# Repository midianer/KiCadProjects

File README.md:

# KiCadProjects
Kicad project eload

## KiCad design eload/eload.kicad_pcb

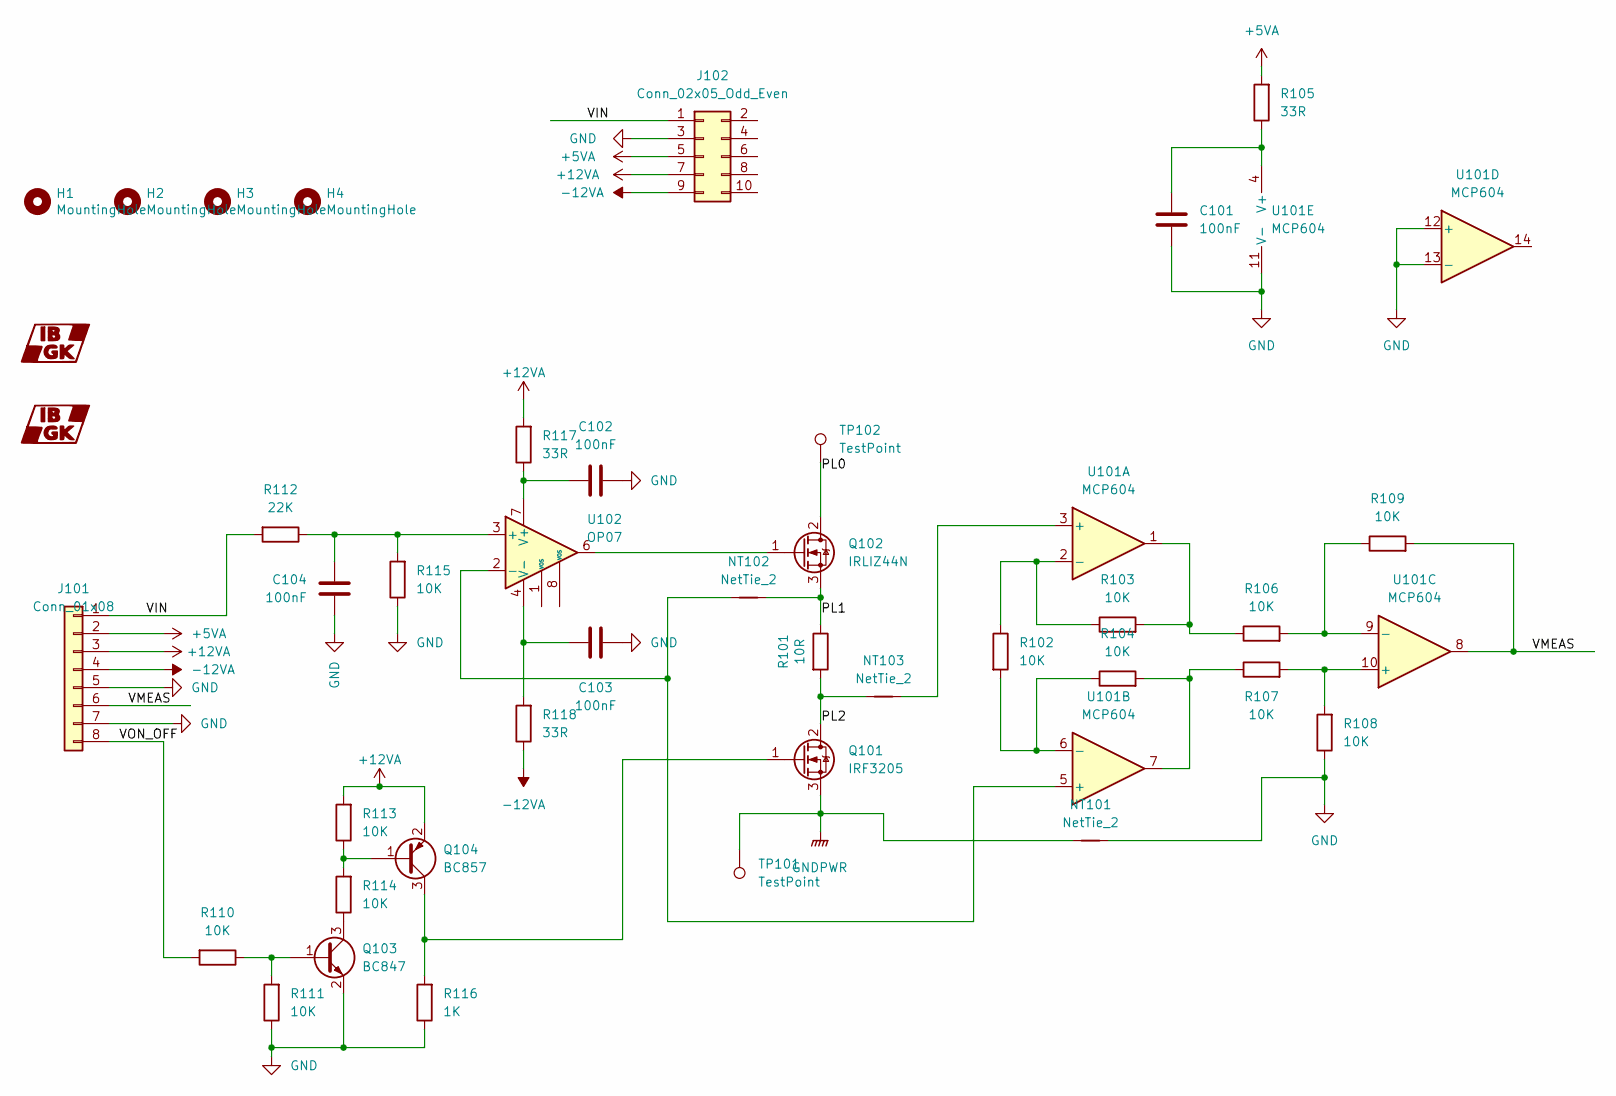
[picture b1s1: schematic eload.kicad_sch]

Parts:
C101, C102, C103, C104: C; C_1206_3216Metric_Pad1.33x1.80mm_HandSolder
G1: LOGO; iblogo
G2: LOGO; iblogo_Cu
H1, H2, H3, H4: MountingHole; MountingHole_3.2mm_M3_Pad_TopBottom
J101: Conn_01x08; PinHeader_1x08_P2.54mm_Vertical
J102: Conn_02x05_Odd_Even; IDC-Header_2x05_P2.54mm_Vertical
NT101, NT102, NT103: NetTie_2; NetTie-2_SMD_Pad0.5mm
Q101: IRF3205; TO-220F-3_Vertical
Q102: IRLIZ44N; TO-220F-3_Vertical
Q103: BC847; SOT-23
Q104: BC857; SOT-23
R101: 10R; R_Axial_Power_L25.0mm_W6.4mm_P27.94mm
R102, R103, R104, R106, R107, R108, R109, R110, R111, R113, R114, R115: 10K; R_0805_2012Metric_Pad1.20x1.40mm_HandSolder
R105, R117, R118: 33R; R_0805_2012Metric_Pad1.20x1.40mm_HandSolder
R112: 22K; R_0805_2012Metric_Pad1.20x1.40mm_HandSolder
R116: 1K; R_0805_2012Metric_Pad1.20x1.40mm_HandSolder
TP101, TP102: TestPoint; TestPoint_THTPad_3.0x3.0mm_Drill1.5mm
U101: MCP604; SO-14_3.9x8.65mm_P1.27mm
U102: OP07; SO-8_3.9x4.9mm_P1.27mm

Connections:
+5VA: J101.2, J102.5, R105.2
+12VA: J101.3, J102.7, Q104.2 (E), R113.2, R117.2
-12VA: J101.4, J102.9, R118.1
/PL0: Q102.2 (D), TP102.1
/PL1: NT102.2, Q102.3 (S), R101.1
/PL2: NT103.1, Q101.2 (D), R101.2
/VIN: J101.1, J102.1, R112.2
/VMEAS: J101.6, R109.2, U101.8
/VON_OFF: J101.8, R110.2
GND: C101.2, C102.2, C103.2, C104.2, J101.5, J101.7, J102.3, NT101.2, Q103.2 (E), R108.1, R111.1, R115.1, R116.1, U101.11 (V-), U101.12 (+), U101.13 (-); also elsewhere on the board
GNDPWR: NT101.1, Q101.3 (S), TP101.1
unnamed 11: C101.1, R105.1, U101.4 (V+); also elsewhere on the board
unnamed 12: C102.1, R117.1, U102.7 (V+); also elsewhere on the board
unnamed 13: C103.1, R118.2, U102.4 (V-); also elsewhere on the board
unnamed 14: C104.1, R112.1, R115.2, U102.3 (+); also elsewhere on the board
unnamed: NT102.1, U101.5 (+), U102.2 (-)
unnamed: Q101.1 (G), Q104.3 (C), R116.2
unnamed: Q102.1 (G), U102.6
unnamed: Q103.1 (B), R110.1, R111.2
unnamed: Q103.3 (C), R114.1
unnamed: Q104.1 (B), R113.1, R114.2
unnamed: R102.1, R103.1, U101.2 (-)
unnamed: R102.2, R104.1, U101.6 (-)
unnamed: R103.2, R106.1, U101.1
unnamed: R104.2, R107.1, U101.7
unnamed: R106.2, R109.1, U101.9 (-)
unnamed: R107.2, R108.2, U101.10 (+)
unnamed: NT103.2, U101.3 (+)

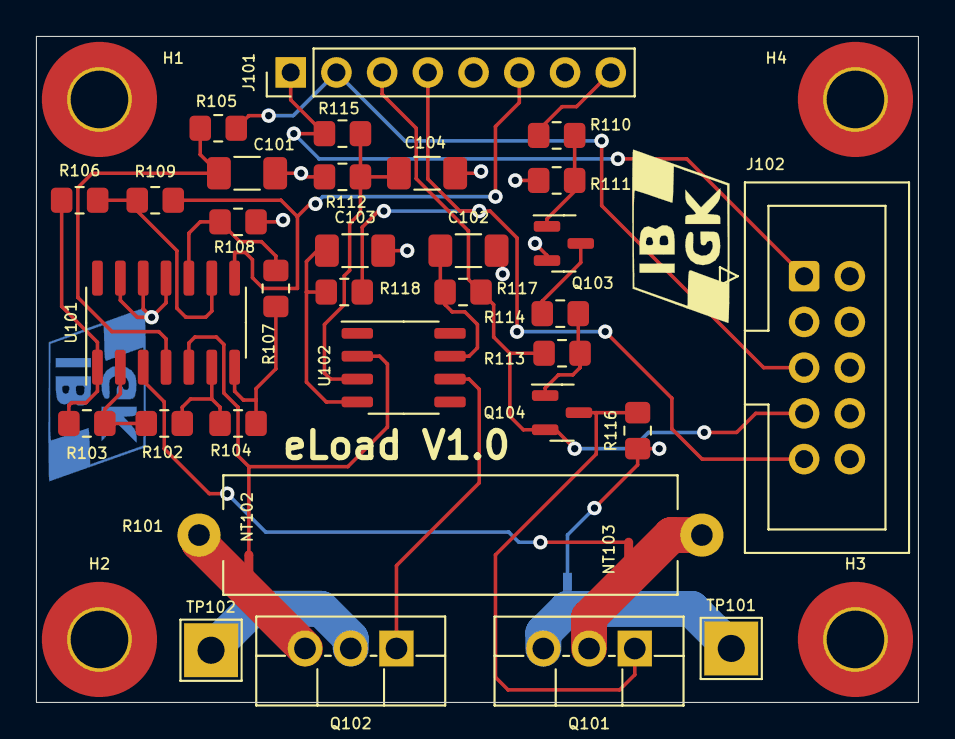
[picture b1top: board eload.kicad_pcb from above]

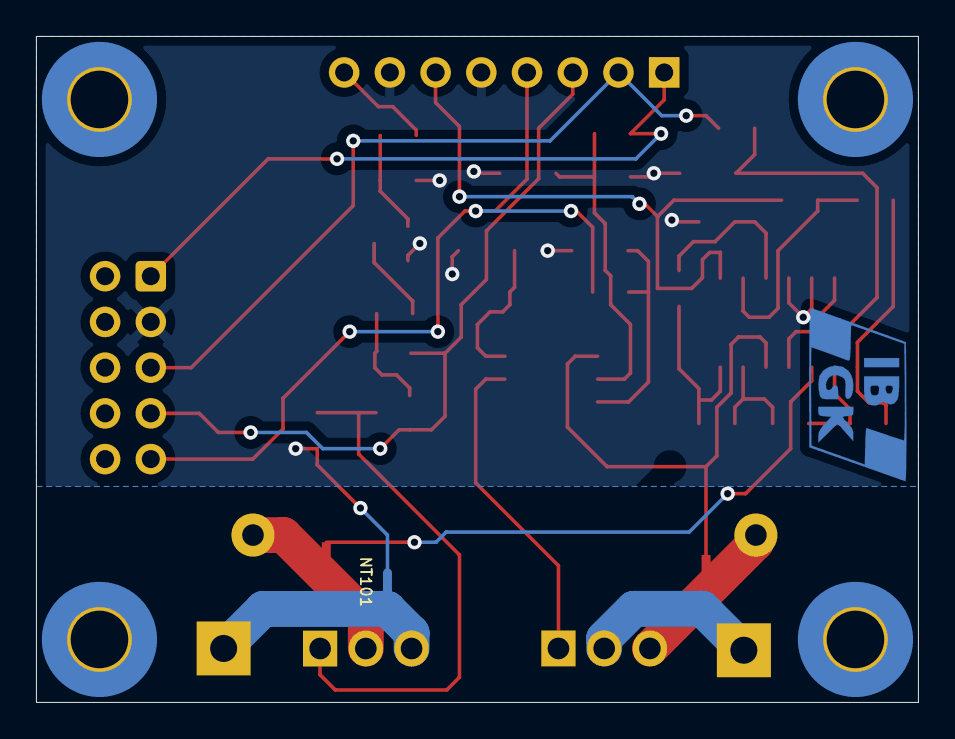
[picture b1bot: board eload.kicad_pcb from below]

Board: 2 copper layers, 49.0 x 37.0 mm, 41 parts (2 on the bottom side), 28 nets.

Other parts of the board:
C?: C; C_1206_3216Metric_Pad1.33x1.80mm_HandSolder
C?#2, C?#3, C?#4: C; C_1206_3216Metric_Pad1.33x1.80mm_HandSolder

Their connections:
GND: C?.2, C?#2.2, C?#3.2, C?#4.2; also elsewhere on the board
unnamed 11: C?#3.1; also elsewhere on the board
unnamed 12: C?#4.1; also elsewhere on the board
unnamed 13: C?.1; also elsewhere on the board
unnamed 14: C?#2.1; also elsewhere on the board

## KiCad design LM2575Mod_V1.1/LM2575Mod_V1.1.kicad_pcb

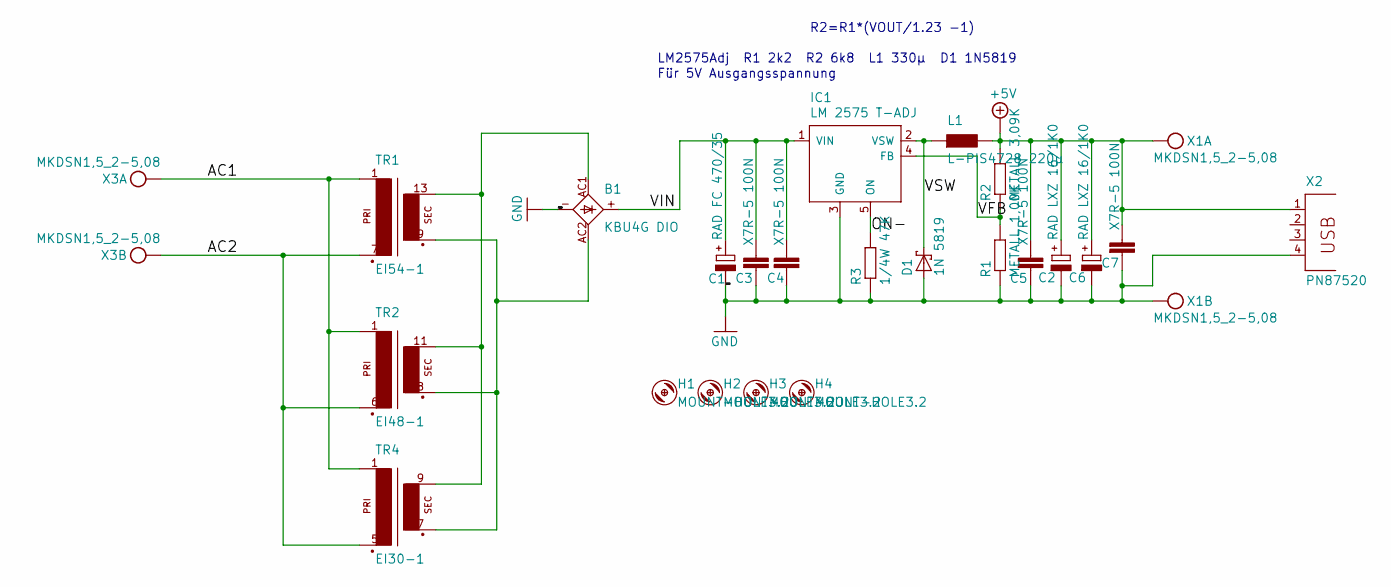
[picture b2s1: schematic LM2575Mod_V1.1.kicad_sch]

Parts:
B1: KBU4G DIO; KBU
C1: RAD FC 470/35; E5-8,5
C2, C6: RAD LXZ 16/1K0; E5-8,5
C3, C4, C5, C7: X7R-5 100N; C050-025X075
D1: 1N 5819; DO35-10-1
H1, H2, H3, H4: MOUNT-HOLE3.2; 3,2
IC1: LM 2575 T-ADJ; TO220-5
L1: L-PIS4728 220µ; PIS4728
R1: METALL 1,00K; 0207_10
R2: METALL 3,09K; 0207_10
R3: 1/4W 47K; 0207_10
TR1: EI54-1
TR2: EI48-1
TR4: EI30-1
X1, X3: MKDSN1,5_2-5,08
X2: PN87520

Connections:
+5V: C2.+, C5.1, C6.+, C7.1, L1.P$2, R2.2, X1.1 (KL), X2.1
/AC1: TR1.1, TR2.1, TR4.1, X3.1 (KL)
/AC2: TR1.7 (P2), TR2.6 (P2), TR4.5 (P2), X3.2 (KL)
/ON-: IC1.5 (ON), R3.2
/VFB: IC1.4 (FB), R1.2, R2.1
/VIN: B1.+, C1.+, C3.1, C4.1, IC1.1 (VIN)
/VSW: D1.C, IC1.2 (VSW), L1.P$1
GND: B1.-, C1.-, C2.-, C3.2, C4.2, C5.2, C6.-, C7.2, D1.A, IC1.3 (GND), R1.1, R3.1, X1.2 (KL), X2.4
unnamed: B1.AC1, TR1.13 (S4), TR2.11 (S4), TR4.9 (S4)
unnamed: B1.AC2, TR1.9 (S3), TR2.8 (S3), TR4.7 (S3)

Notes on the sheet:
Für 5V Ausgangsspannung
LM2575Adj R1 2k2 R2 6k8 L1 330µ D1 1N5819
R2=R1*(VOUT/1.23 -1)

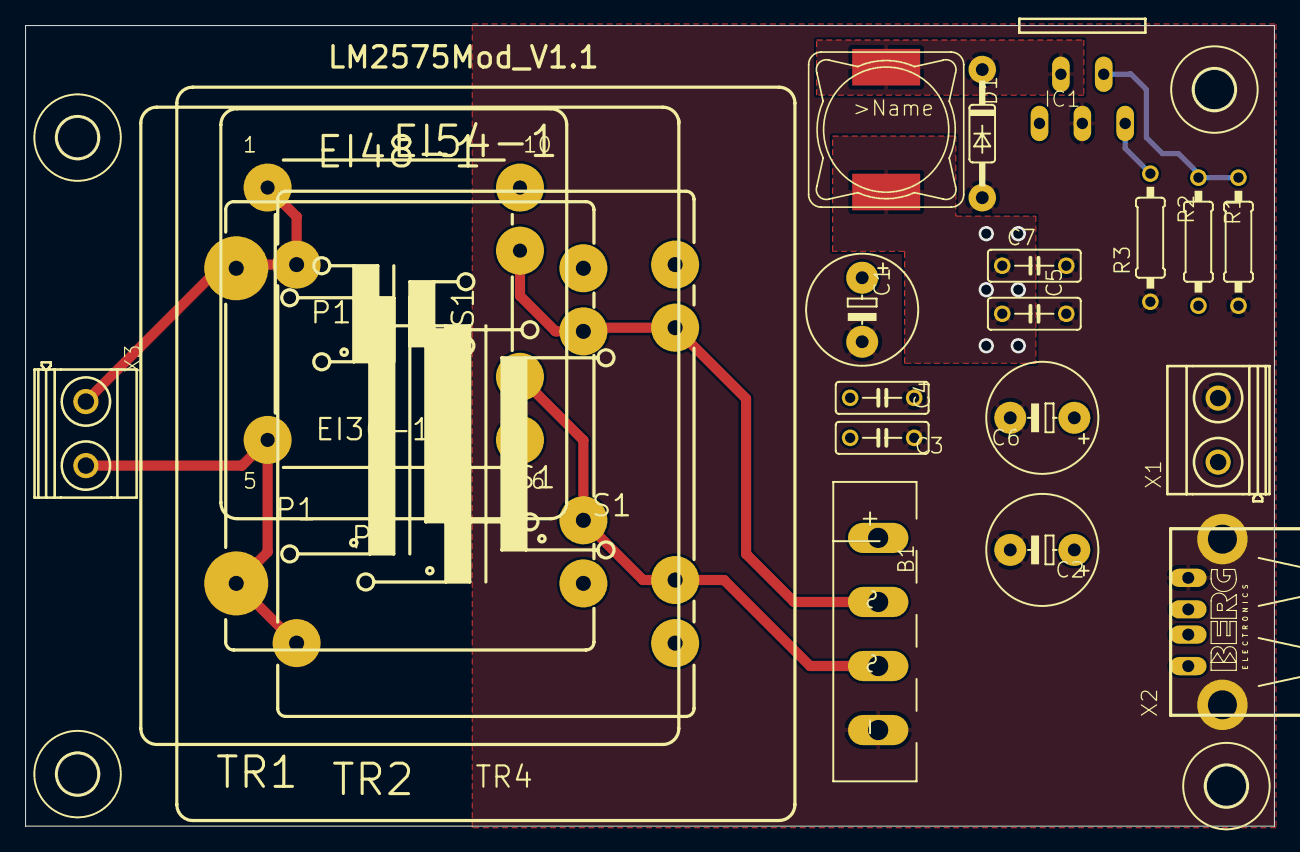
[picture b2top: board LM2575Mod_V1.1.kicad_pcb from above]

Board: 2 copper layers, 99.1 x 63.5 mm, 24 parts (0 on the bottom side), 10 nets.

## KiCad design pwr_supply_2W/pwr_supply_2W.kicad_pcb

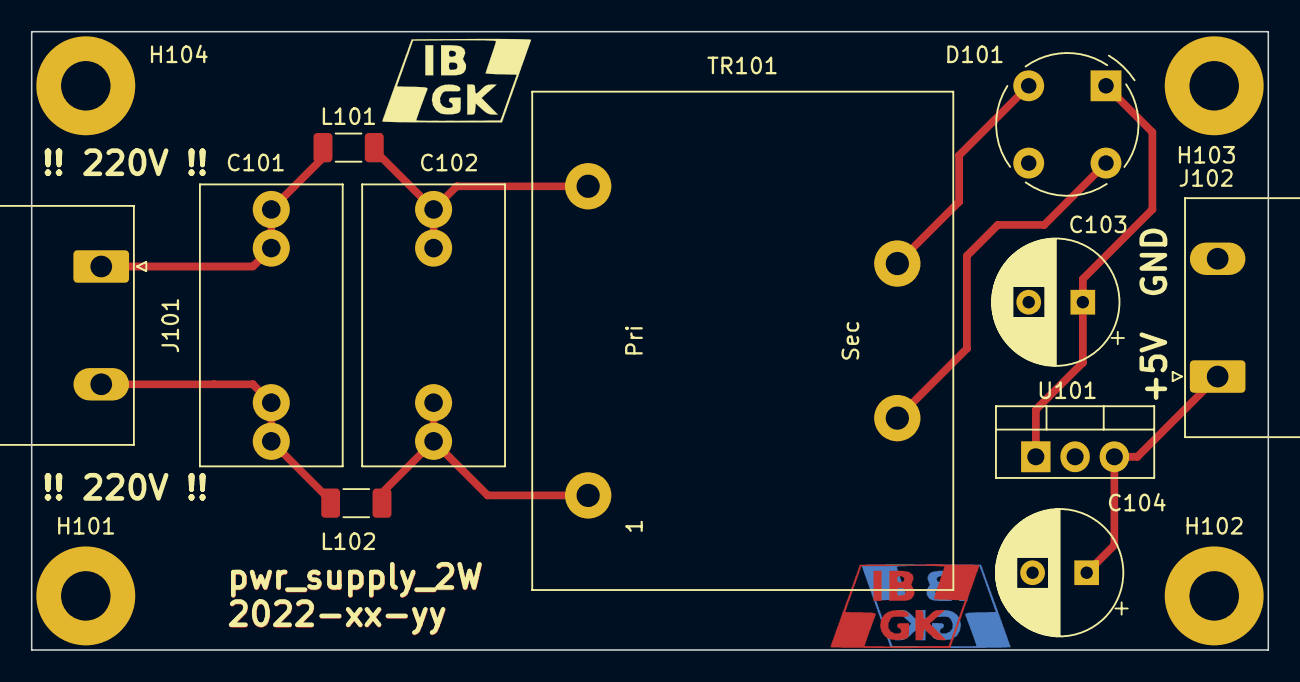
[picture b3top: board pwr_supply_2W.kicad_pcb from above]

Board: 2 copper layers, 80.0 x 40.0 mm, 18 parts (1 on the bottom side), 9 nets.

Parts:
C101: 100nF; C_Rect_L18.0mm_W9.0mm_P15.00mm_FKS3_FKP3
C104: 470uF/25V; CP_Radial_D8.0mm_P3.50mm
C?: C; C_Rect_L18.0mm_W9.0mm_P15.00mm_FKS3_FKP3
C?#2: 470uF/25V; CP_Radial_D8.0mm_P3.50mm
D?: D_Bridge_+A-A; Diode_Bridge_Round_D9.0mm
G101: LOGO; iblogo
G102, G103: LOGO; iblogo_Cu
H101, H102, H103, H104: MountingHole; MountingHole_3.2mm_M3_Pad
J?: Conn_01x02; PhoenixContact_GMSTBA_2,5_2-G-7,62_1x02_P7.62mm_Horizontal
J?#2: Conn_01x02; PhoenixContact_GMSTBA_2,5_2-G-7,62_1x02_P7.62mm_Horizontal
L102: BLM31 100u; L_1206_3216Metric_Pad1.22x1.90mm_HandSolder
L?: L; L_1206_3216Metric_Pad1.22x1.90mm_HandSolder
TR101: EI30/18 9V; Transformer_CHK_EI30-2VA_1xSec
U?: LM7805_TO220; TO-220-3_Vertical

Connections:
/220V_AC1: C101.1, J?#2.1, L?.1
/220V_AC1_F: C?.1, L?.2, TR101.1
/220V_AC2: C101.2, J?#2.2, L102.1
/220V_AC2_F: C?.2, L102.2, TR101.5
/+5V: C104.1, J?.1, U?.3 (VO)
/AC1: D?.4, TR101.7
/AC2: D?.2, TR101.9
/GND: C104.2, C?#2.2, D?.3 (-), J?.2, U?.2 (GND)
/VP: C?#2.1, D?.1 (+), U?.1 (VI)

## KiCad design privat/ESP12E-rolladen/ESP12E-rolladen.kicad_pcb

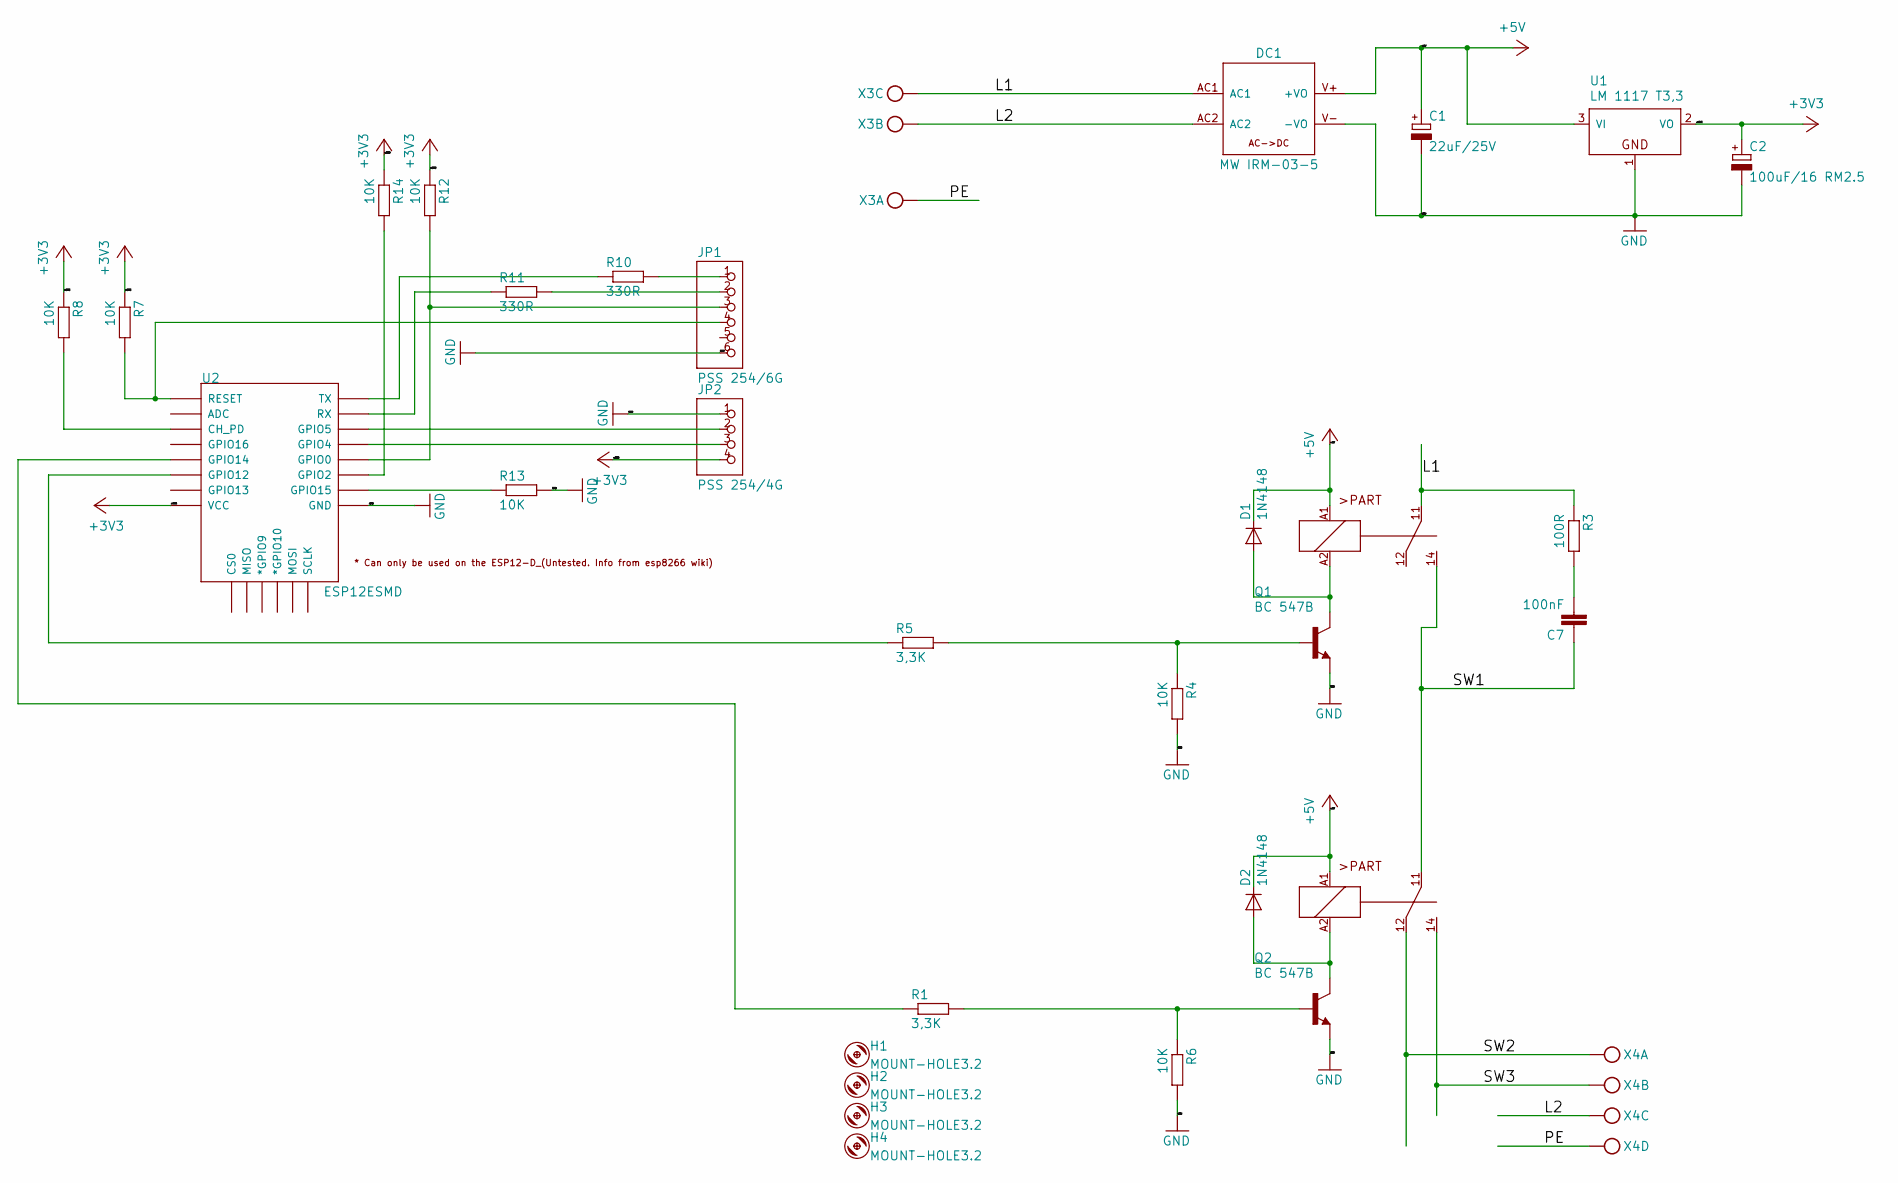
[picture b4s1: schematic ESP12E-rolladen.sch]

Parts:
C1: 22uF/25V; CRAD_E2,5-6
C2: 100uF/16 RM2.5; CRAD_E2,5-6
C7: 100nF; C150-054X183
D1, D2: 1N4148; 1N4148-DO35_4
DC1: MW IRM-03-5; MW_IRM03
H1, H2, H3, H4: MOUNT-HOLE3.2; 3,2
JP1: PSS 254/6G; 1X06
JP2: PSS 254/4G; 1X04
K2, K3: FTR LYCA 005V; FTR_LY
Q1, Q2: BC 547B; TO92
R1, R5: 3,3K; R1206
R3: 100R; 0411_15
R4, R6, R7, R8, R12, R13, R14: 10K; R1206
R10, R11: 330R; R1206
U1: LM 1117 T3,3; TO220S
U2: ESP12ESMD; ESP12E-SMD
X3: MKDSN1,5_3-5,08
X4: MKDSN1,5_4-5,08

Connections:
+3V3: C2.+, JP2.4, R7.1, R8.1, R12.1, R14.1, U1.2 (VO), U2.VCC
+5V: C1.+, D1.K, D2.K, DC1.V+ (+VO), K2.A1 (1), K3.A1 (1), U1.3 (VI)
/L1: DC1.AC1, K3.11 (S1), R3.1, X3.3
/L2: DC1.AC2, X3.2, X4.3
/PE: X3.1, X4.4
/SW1: C7.1, K2.11 (S1), K3.14 (A1)
/SW2: K2.12 (R1), X4.1
/SW3: K2.14 (A1), X4.2
GND: C1.-, C2.-, DC1.V- (-VO), JP1.6, JP2.1, Q1.1 (E), Q2.1 (E), R4.2, R6.2, R13.2, U1.1 (GND), U2.GND
unnamed: C7.2, R3.2
unnamed: D1.A, K3.A2 (2), Q1.3 (C)
unnamed: D2.A, K2.A2 (2), Q2.3 (C)
unnamed: JP1.1, R10.2
unnamed: JP1.2, R11.2
unnamed: JP1.3, R12.2, U2.GPIO0
unnamed: JP1.4, R7.2, U2.RESET
unnamed: JP2.2, U2.GPIO5
unnamed: JP2.3, U2.GPIO4
unnamed: Q1.2 (B), R4.1, R5.2
unnamed: Q2.2 (B), R1.2, R6.1
unnamed: R1.1, U2.GPIO14
unnamed: R5.1, U2.GPIO12
unnamed: R8.2, U2.CH_PD
unnamed: R10.1, U2.TXD0 (TX)
unnamed: R11.1, U2.RXD0 (RX)
unnamed: R13.1, U2.GPIO15
unnamed: R14.2, U2.GPIO2

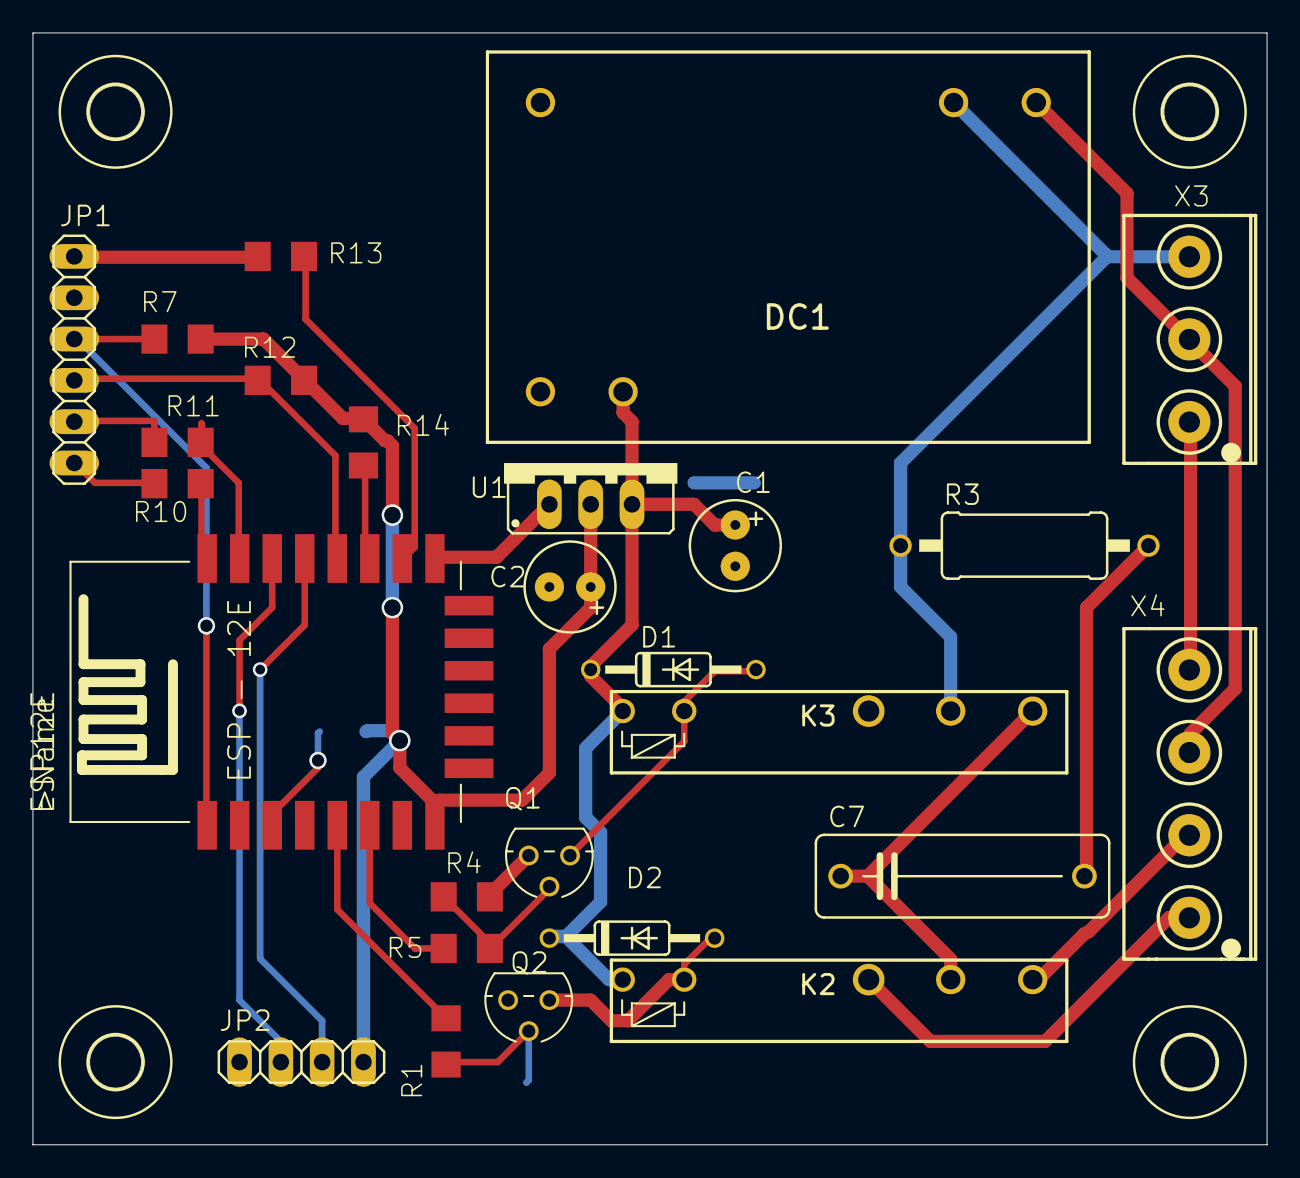
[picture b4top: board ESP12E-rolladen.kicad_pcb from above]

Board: 2 copper layers, 75.9 x 68.3 mm, 32 parts (0 on the bottom side), 27 nets.

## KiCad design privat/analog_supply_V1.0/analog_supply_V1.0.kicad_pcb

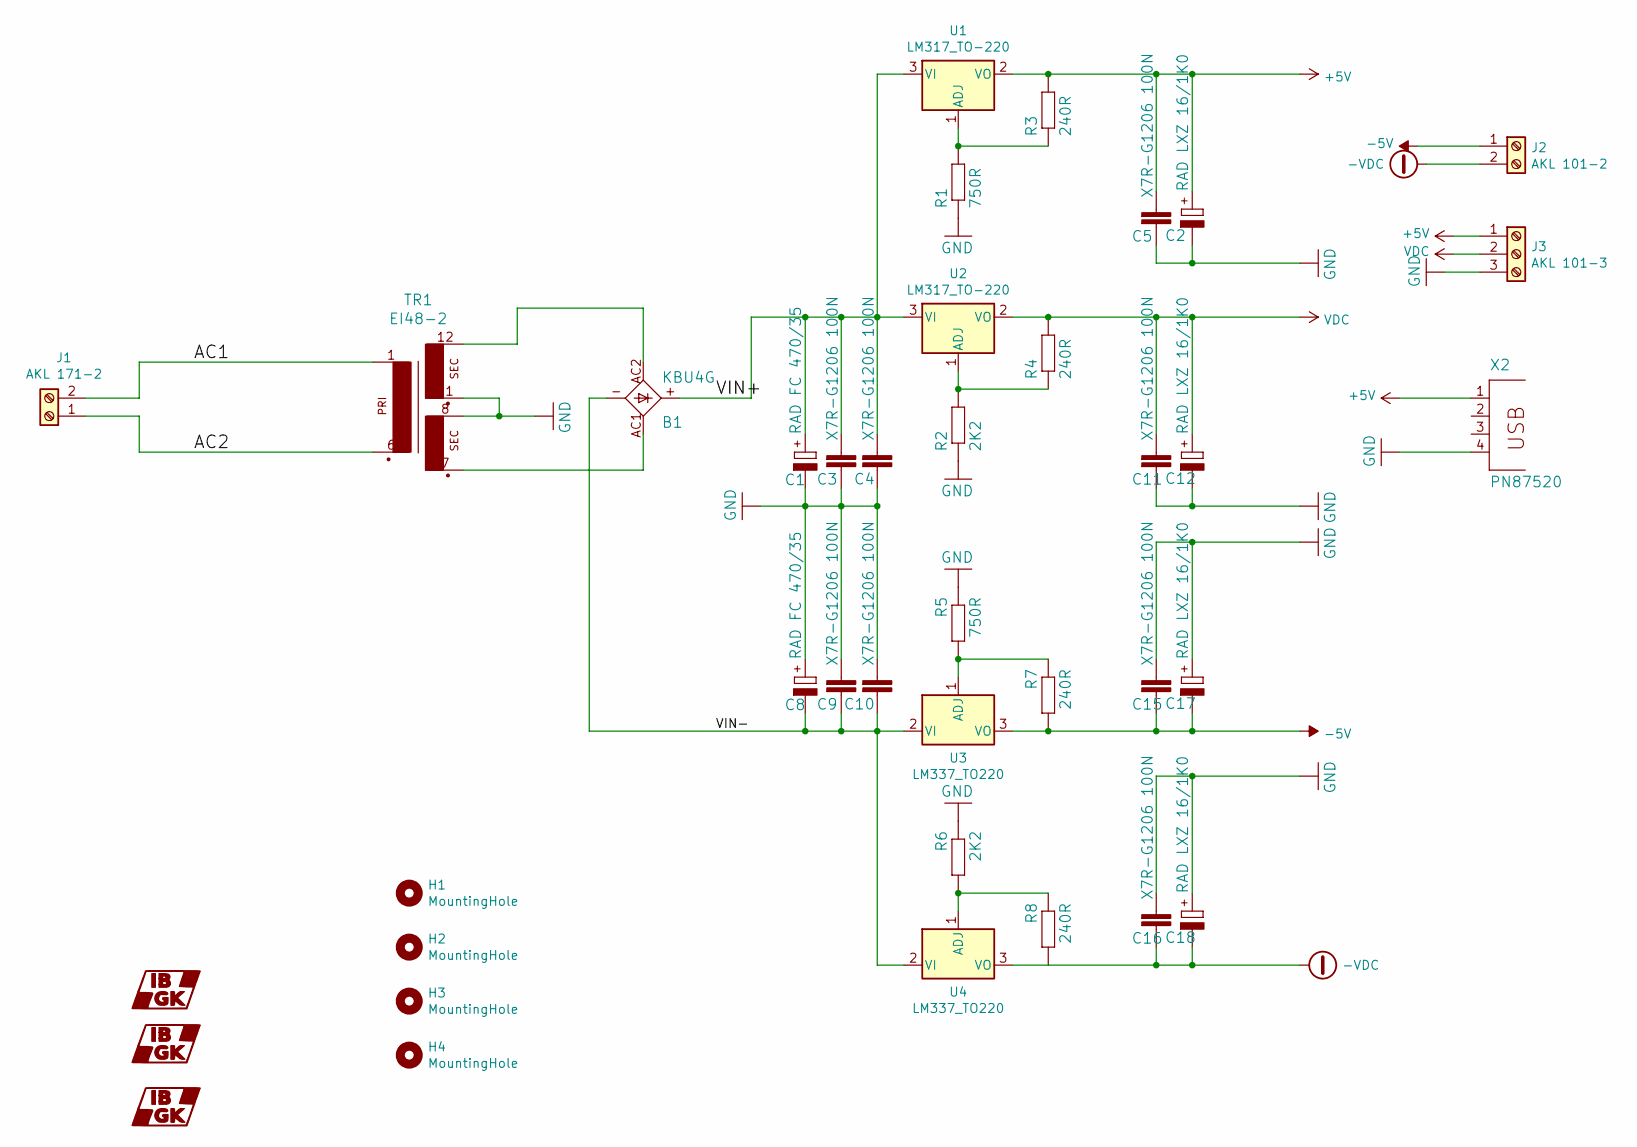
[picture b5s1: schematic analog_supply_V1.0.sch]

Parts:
B1: KBU4G; KBU
C1, C8: RAD FC 470/35; E5-8,5
C2, C12, C17, C18: RAD LXZ 16/1K0; E5-8,5
C3, C4, C5, C9, C10, C11, C15, C16: X7R-G1206 100N; C_1206_3216Metric_Pad1.33x1.80mm_HandSolder
G1: LOGO; iblogo
G2, G3: LOGO; iblogo_Cu
H1, H2, H3, H4: MountingHole; MountingHole_3.2mm_M3_DIN965_Pad
J1: AKL 171-2; TerminalBlock_RND_205-00067_1x02_P7.50mm_Horizontal
J2: AKL 101-2; TerminalBlock_Phoenix_MKDS-1,5-2_1x02_P5.00mm_Horizontal
J3: AKL 101-3; TerminalBlock_Phoenix_MKDS-1,5-3_1x03_P5.00mm_Horizontal
R1, R5: 750R; R_1206_3216Metric_Pad1.30x1.75mm_HandSolder
R2, R6: 2K2; R_1206_3216Metric_Pad1.30x1.75mm_HandSolder
R3, R4, R7, R8: 240R; R_1206_3216Metric_Pad1.30x1.75mm_HandSolder
TR1: EI48-2; EI48-1
U1, U2: LM317_TO-220; TO-220-3_Vertical
U3, U4: LM337_TO220; TO-220-3_Vertical
X2: PN87520

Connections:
+5V: C2.+, C5.1, J3.1, R3.2, U1.2 (VO), X2.1
-5V: C15.2, C17.-, J2.1, R7.2, U3.3 (VO)
-VDC: C16.2, C18.-, J2.2, R8.2, U4.3 (VO)
/AC1: J1.2, TR1.1
/AC2: J1.1, TR1.6 (P2)
/VIN+: B1.+, C1.+, C3.1, C4.1, U1.3 (VI), U2.3 (VI)
/VIN-: B1.-, C8.-, C9.2, C10.2, U3.2 (VI), U4.2 (VI)
GND: C1.-, C2.-, C3.2, C4.2, C5.2, C8.+, C9.1, C10.1, C11.2, C12.-, C15.1, C16.1, C17.+, C18.+, J3.3, R1.1, R2.1, R5.1, R6.1, TR1.8 (S4), TR1.11 (S5), X2.4
unnamed: B1.AC1, TR1.7 (S3)
unnamed: B1.AC2, TR1.12 (S6)
unnamed: R1.2, R3.1, U1.1 (ADJ)
unnamed: R2.2, R4.1, U2.1 (ADJ)
unnamed: R5.2, R7.1, U3.1 (ADJ)
unnamed: R6.2, R8.1, U4.1 (ADJ)
VDC: C11.1, C12.+, J3.2, R4.2, U2.2 (VO)

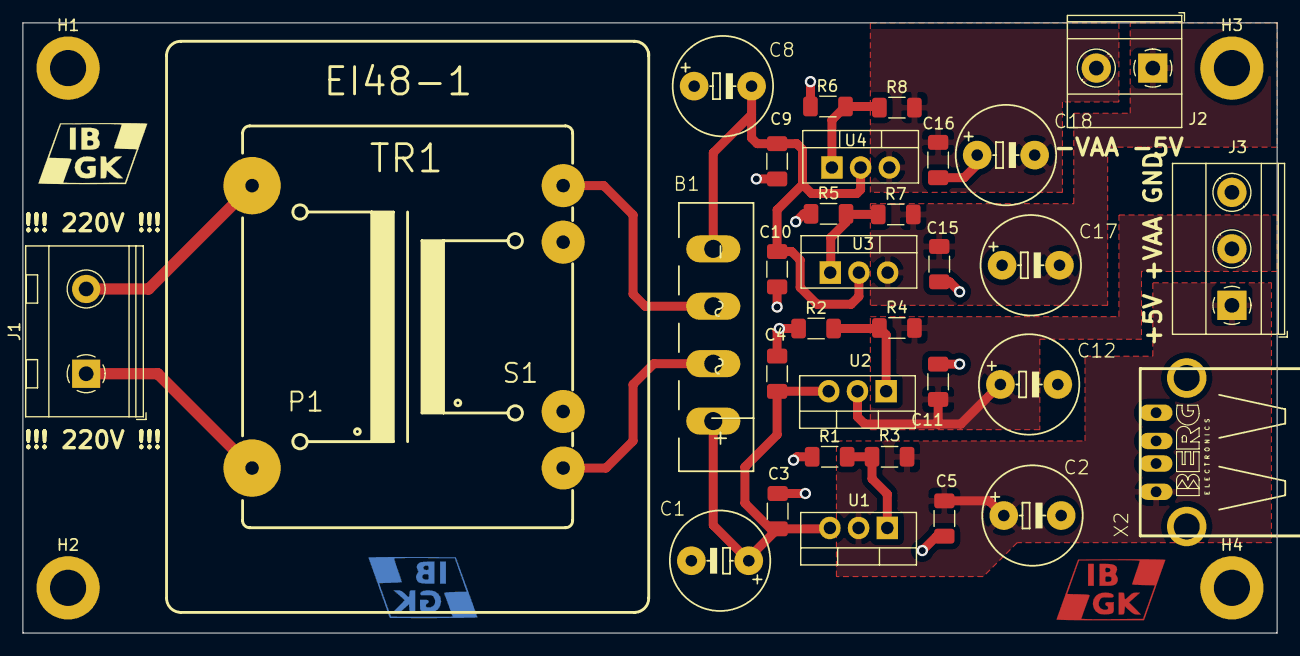
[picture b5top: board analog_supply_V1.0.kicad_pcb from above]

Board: 2 copper layers, 111.0 x 54.0 mm, 39 parts (1 on the bottom side), 15 nets.

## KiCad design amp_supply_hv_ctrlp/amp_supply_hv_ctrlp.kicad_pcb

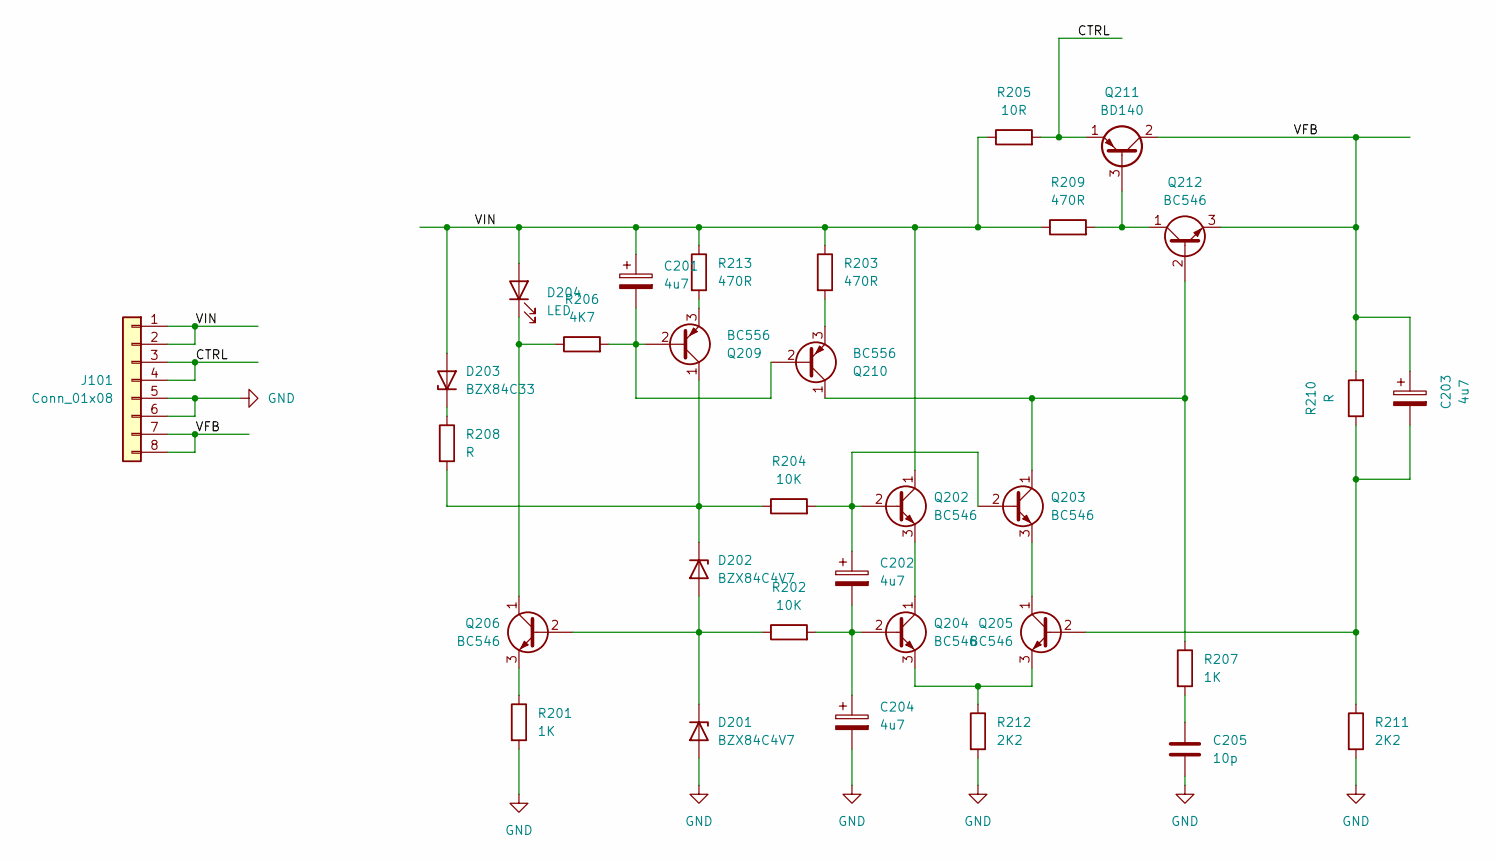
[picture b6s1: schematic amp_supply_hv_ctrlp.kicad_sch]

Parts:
C201, C202, C203, C204: 4u7; CP_Radial_D5.0mm_P2.50mm
C205: 10p; C_0805_2012Metric_Pad1.18x1.45mm_HandSolder
D201, D202: BZX84C4V7; D_SOT-23_ANK
D203: BZX84C33; D_SOT-23_ANK
D204: LED; LED_1206_3216Metric_Pad1.42x1.75mm_HandSolder
J101: Conn_01x08; PinHeader_1x08_P2.54mm_Vertical
Q202, Q203, Q204, Q205, Q206, Q212: BC546; TO-92_Inline
Q209, Q210: BC556; TO-92_Inline
Q211: BD140; TO-126-3_Vertical
R201, R207: 1K; R_1206_3216Metric_Pad1.30x1.75mm_HandSolder
R202, R204: 10K; R_1206_3216Metric_Pad1.30x1.75mm_HandSolder
R203, R209, R213: 470R; R_1206_3216Metric_Pad1.30x1.75mm_HandSolder
R205: 10R; R_1206_3216Metric_Pad1.30x1.75mm_HandSolder
R206: 4K7; R_1206_3216Metric_Pad1.30x1.75mm_HandSolder
R208, R210: R; R_1206_3216Metric_Pad1.30x1.75mm_HandSolder
R211, R212: 2K2; R_1206_3216Metric_Pad1.30x1.75mm_HandSolder

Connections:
/CTRL: J101.3, J101.4, Q211.1 (E), R205.2; also elsewhere on the board
/VFB: C203.1, J101.7, J101.8, Q211.2 (C), Q212.3 (E), R210.2; also elsewhere on the board
/VIN: C201.1, D203.2 (A), D204.2 (A), J101.1, J101.2, Q202.1 (C), R203.1, R205.1, R209.1, R213.1
GND: C204.2, C205.2, D201.2 (A), J101.5, J101.6, R201.2, R211.2, R212.2; also elsewhere on the board
unnamed: C201.2, Q209.2 (B), Q210.2 (B), R206.2
unnamed: C202.1, Q202.2 (B), Q203.2 (B), R204.2
unnamed: C202.2, C204.1, Q204.2 (B), R202.2
unnamed: C203.2, Q205.2 (B), R210.1, R211.1
unnamed 8: C205.1, R207.2; also elsewhere on the board
unnamed: D201.1 (K), D202.2 (A), Q206.2 (B), R202.1
unnamed: D202.1 (K), Q209.1 (C), R204.1, R208.2
unnamed: D203.1 (K), R208.1
unnamed: D204.1 (K), Q206.1 (C), R206.1
unnamed: Q202.3 (E), Q204.1 (C)
unnamed: Q203.1 (C), Q210.1 (C), Q212.2 (B), R207.1
unnamed: Q203.3 (E), Q205.1 (C)
unnamed: Q204.3 (E), Q205.3 (E), R212.1
unnamed: Q206.3 (E), R201.1
unnamed: Q209.3 (E), R213.2
unnamed: Q210.3 (E), R203.2
unnamed 20: Q211.3 (B), Q212.1 (C), R209.2; also elsewhere on the board

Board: 2 copper layers, 32 parts (0 on the bottom side), 21 nets, no tracks yet.

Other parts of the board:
C?: 10p; C_0805_2012Metric_Pad1.18x1.45mm_HandSolder
Q?: BD140; TO-126-3_Vertical

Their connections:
/CTRL: Q?.1 (E); also elsewhere on the board
/VFB: Q?.2 (C); also elsewhere on the board
GND: C?.2; also elsewhere on the board
unnamed 8: C?.1; also elsewhere on the board
unnamed 20: Q?.3 (B); also elsewhere on the board

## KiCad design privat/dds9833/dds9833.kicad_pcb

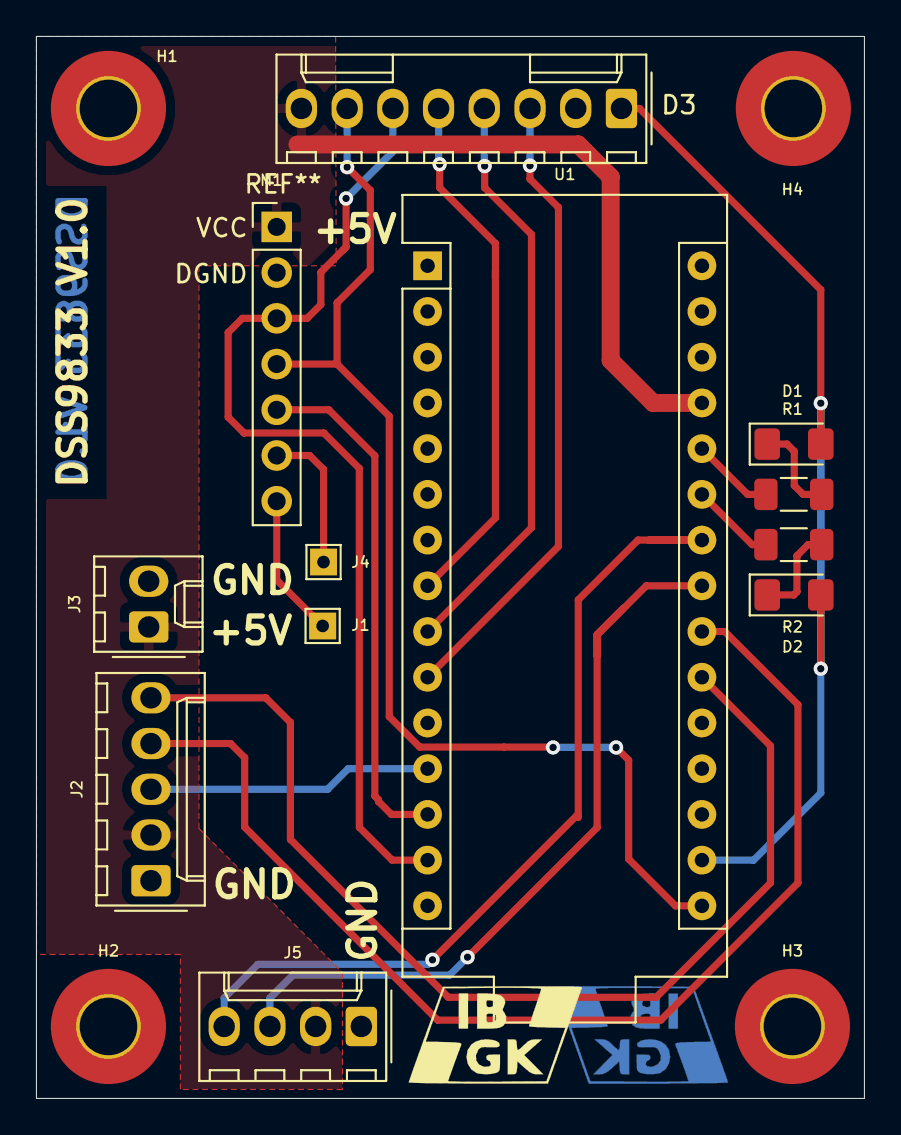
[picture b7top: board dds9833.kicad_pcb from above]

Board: 2 copper layers, 46.0 x 59.0 mm, 18 parts (1 on the bottom side), 20 nets.

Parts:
D1, D2: LED; D_1206_3216Metric_Pad1.42x1.75mm_HandSolder
D3: TFT1_8; Molex_KK-254_AE-6410-08A_1x08_P2.54mm_Vertical
G1: LOGO; iblogo
G2: LOGO; iblogo_Cu
H1, H2, H3, H4: MountingHole; MountingHole_3.2mm_M3_Pad_TopBottom
J1: AOUT; TestPoint_THTPad_1.5x1.5mm_Drill0.7mm
J2: KY040-2ROW; KY040_Vertical
J3: Conn_01x02; Molex_KK-254_AE-6410-02A_1x02_P2.54mm_Vertical
J4: AGND; TestPoint_THTPad_1.5x1.5mm_Drill0.7mm
J5: I2C Display; Molex_KK-254_AE-6410-04A_1x04_P2.54mm_Vertical
M1: DDS9833; AD9833Mod
R1, R2: 330R; R_1206_3216Metric_Pad1.30x1.75mm_HandSolder
U1: Arduino_Nano

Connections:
+5V: D3.8, J2.2, J3.1, J5.2, M1.1, U1.27
/SDA: J5.3, U1.23
/lSCL: J5.4, U1.24
GND: D3.2, J2.1, J3.2, J5.1, M1.2, U1.29
unnamed: D1.1, R1.1
unnamed: D1.2, D2.2, D3.1, U1.17
unnamed: D2.1, R2.1
unnamed: D3.3, U1.10
unnamed: D3.4, U1.9
unnamed: D3.5, U1.8
unnamed: D3.6, M1.3, U1.14
unnamed: D3.7, M1.4, U1.16
unnamed: J1.1, M1.7
unnamed: J2.3, U1.12
unnamed: J2.4, U1.22
unnamed: J2.5, U1.21
unnamed: J4.1, M1.6
unnamed: M1.5, U1.13
unnamed: R1.2, U1.26
unnamed: R2.2, U1.25

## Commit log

2022-03-06 Initial commit dds9833 analog_supply_V1.0
2022-03-06 Initial commit ibgk-lib
2022-09-04 initial project/amp_supply_hv_ctrlp
2022-09-06 analog_supply_V1.0 add order numbers
2022-09-17 neu: LM2575Mod_V1.1 ESP12E-rolladen_V1.0 ESP12E-rolladen(V1.1)
2022-11-01 initial pwr_supply_2W; PCB Version 2022-10-16
2022-11-01 remove unused
2022-11-01 CP footprint for C103/C104
2022-12-21 initial lm2575_pwr V5
2022-12-21 lm2575_pwr V6
2023-02-07 eload V1.0
2023-02-07 eload V1.0 updated measure connections
2023-11-16 initial ledx8
